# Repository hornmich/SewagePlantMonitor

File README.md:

# SewagePlantMonitor
The protection and monitoring unit for belt based sewage plants

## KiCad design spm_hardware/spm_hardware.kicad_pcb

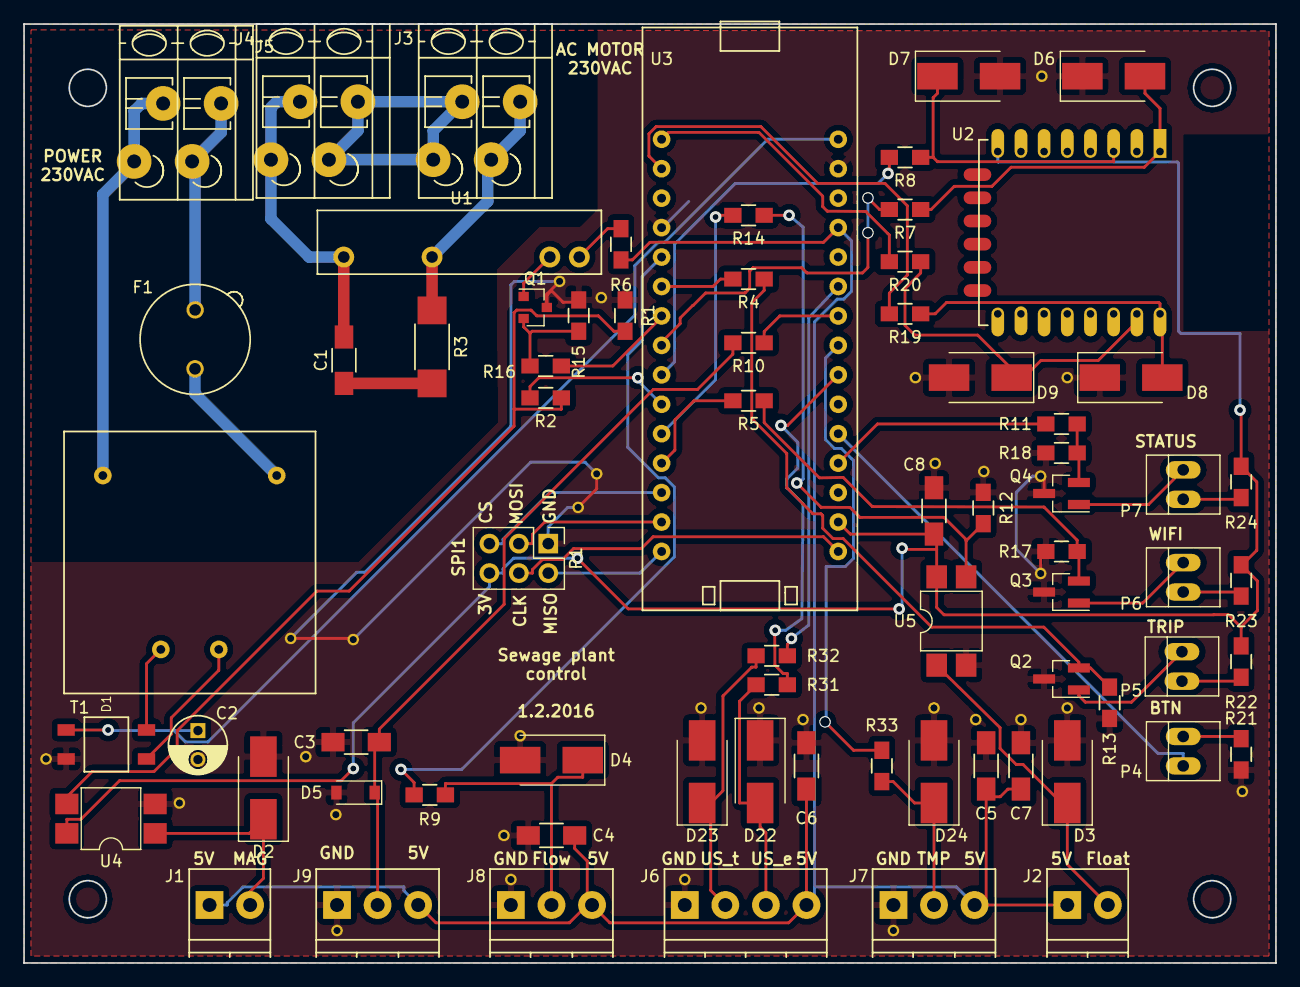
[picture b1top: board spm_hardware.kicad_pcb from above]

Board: 2 copper layers, 108.0 x 81.0 mm, 72 parts (0 on the bottom side), 59 nets.

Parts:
C1, C3, C4, C5, C6, C7, C8: C; C_1206_HandSoldering
C2: CP; C_Radial_D5_L11_P2.5
D1: D_Bridge_+-AA; D-HD04
D2, D3, D4, D6, D7, D8, D9, D22, D23, D24: D_TVS; D_SMB_Handsoldering
D5: D_Zener; D_SOD-123
F1: Fuse; Fuseholder_Fuse_TR5_Littlefuse-No560_No460
J1: Magnet sensor; TerminalBlock_Pheonix_PT-3.5mm_2pol
J2: Floater; TerminalBlock_Pheonix_PT-3.5mm_2pol
J3: MotIn; TerminalBlock_WAGO-804_RM5mm_2pol
J4: MotOut; TerminalBlock_WAGO-804_RM5mm_2pol
J5: 230VAC; TerminalBlock_WAGO-804_RM5mm_2pol
J6: USonic sensor; TerminalBlock_Pheonix_PT-3.5mm_4pol
J7: Temp&Humid sensor; TerminalBlock_Pheonix_PT-3.5mm_3pol
J8: Flow sensor; TerminalBlock_Pheonix_PT-3.5mm_3pol
J9: HAL sensor; TerminalBlock_Pheonix_PT-3.5mm_3pol
P1: DIL6; Pin_Header_Straight_2x03_Pitch2.54mm
P4, P5, P6, P7: CONN_01X02; PINHEAD1-2
Q1: BS170; SOT-23
Q2, Q3, Q4: Q_NMOS_DGS; SOT-23_Handsoldering
R1, R2, R4, R5, R6, R7, R8, R9, R10, R11, R12, R13, R14, R15, R16, R17, R18, R19, R20, R21, R22, R23, R24, R31, R32, R33: R; R_0805_HandSoldering
R3: R; R_2010_HandSoldering
T1: Transformer_1P_1S; BV_201_0145
U1: G3MB-202P
U2: ESP-12E
U3: STM32L432
U4, U5: LTV-817; DIP-4_W7.62mm_SMD

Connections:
+3V3: C8.1, P1.6, R22.2, R23.2, R24.2, U2.8, U3.29, U4.4, U5.4
+5V: C4.1, C5.1, C6.1, C7.1, J1.1, J2.1, J6.4, J7.3, J8.3, J9.3, R6.1, U3.19
+12V: C2.1, D1.1, U3.16
Btn_ctrl: P4.1, U3.26
Floater: R14.1, U3.11
Flow_Sen: R9.2, U3.5
GND: C2.2, C3.2, C4.2, C5.2, C6.2, C7.2, C8.2, D1.2, D2.2, D3.2, D4.2, D5.2, D6.1, D7.2, D8.1, D9.2, D22.1, D23.2, D24.2, J6.1, J7.1, J8.1, J9.1, P1.1, Q1.3, Q2.3, Q3.3, Q4.3, R1.2, R12.2, R13.1, R15.2, R17.1, R18.1, R21.1, U2.9, U3.4, U3.17, U4.2, U5.2
HAL_Sen: R10.1, U3.22
LED_Status: R11.2, U3.27
LED_Trip: R4.2, U3.6
LED_WiFi: R5.2, U3.12
MOT_Off: R16.1, U3.7
Mag_Sw: R2.1, U3.10
unnamed: C1.1, R3.1
unnamed: C1.2, J4.2, U1.1
unnamed: C3.1, D5.1, J9.2, R10.2
unnamed: D1.3, T1.4
unnamed: D1.4, T1.3
unnamed: D2.1, J1.2, U4.1
unnamed: D3.1, J2.2, U5.1
unnamed: D4.1, J8.2, R9.1
unnamed: D6.2, R7.1, U2.1
unnamed: D7.1, R8.1, U2.3
unnamed: D8.2, R19.2, U2.16
unnamed: D9.1, R20.2, U2.15
unnamed: D22.2, J6.3, R31.1
unnamed: D23.1, J6.2, R32.1
unnamed: D24.1, J7.2, R33.1
unnamed: F1.1, T1.1
unnamed: F1.2, J5.1
unnamed: J3.1, R3.2, U1.2
unnamed: J3.2, J4.1
unnamed: J5.2, T1.2
unnamed: P4.2, R21.2
unnamed: P5.1, R22.1
unnamed: P5.2, Q2.1
unnamed: P6.1, R23.1
unnamed: P6.2, Q3.1
unnamed: P7.1, R24.1
unnamed: P7.2, Q4.1
unnamed: Q1.1, U1.3
unnamed: Q1.2, R15.1, R16.2
unnamed: Q2.2, R4.1, R13.2
unnamed: Q3.2, R5.1, R17.2
unnamed: Q4.2, R11.1, R18.2
unnamed: R1.1, R2.2, U4.3
unnamed: R6.2, U1.4
unnamed: R12.1, R14.2, U5.3
SPI_CLK: P1.4, U3.30
SPI_CS: P1.5, U3.13
SPI_MISO: P1.2, U3.15
SPI_MOSI: P1.3, U3.14
TH_Sensor: R33.2, U3.23
USART1_RX: R19.1, U3.2
USART1_TX: R20.1, U3.1
USonic_echo: R31.2, U3.24
USonic_trigger: R32.2, U3.21
WIFI_EN: R8.2, U3.9
WIFI_RST: R7.2, U3.8

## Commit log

2016-11-15 Integrate the Ultrasonic module
    This firmware creates a simple distance measuring device by using
    JSN-SR04T ultrasonic module.
2016-12-16 Update ultrasonic sensor driver
2016-12-24 add hardware design sketch
2016-12-24 add RTOS middleware
2017-01-02 Add solid state relay to library
2017-01-02 Improve schematics
    * Add solid state relay
    * Add transformer and simple power circuit
    * Fix varistors
2017-01-03 add diode rectifier bridge footprint
2017-01-03 add transformer footprint
2017-01-03 exchange varistors for transils
2017-01-03 assign footprints to components
2017-01-03 create first attempt of PCB design
    Still almost empty
2017-01-03 update packages
2017-01-07 Add footprints of components
2017-01-07 Create PCB sketch
2017-01-27 Place components on PCB
2017-01-27 Add submodule for ESP8266
2017-01-27 Fix .gitignore
2017-01-27 Change transils and diodes packages to smaller
2017-01-27 Change fuse for smaller one
2017-01-28 Layout the PCB
2017-01-28 Add autorouter products to gitignore
2017-01-28 Remove temporary file
2017-02-01 Adapt the PCB layout for a box
2017-02-09 Change UART pins and improve PCB layout
2017-02-20 PCB design improved
2017-03-06 Add custom vias and apply on PCB
